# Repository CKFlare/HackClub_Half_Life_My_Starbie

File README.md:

# HackClub Half Life: My Starbie

This week I made the starter project, a starbie.

my Starbie is BMO from adventure time. during the second week I will create a housing for it that resembles him from the show. I chose BMO simply because he is cute and I thought it was a good fit as he is a robot.

My starbie is very simple, it is just the basic starbie but with a passive buzzer added so it can react with sounds. I simply use the passive buzzer which is in the Arduino Uno R3 super starter kit so that I could buy as little as possible. This entire project is very simple honestly, I didn't do anything special other than put things on the backside of the pcb which is not described in the week one tutorial, still very simple though. this means all it has is:

- a 128x64 pixel screen
- a motion sensor
- a tempurature and humdity sensor
- 2 push buttons

sorry for the horribly ugly schematic

*I own the passive buzzer and the DHT11 therefore they are not found in the bill of materials

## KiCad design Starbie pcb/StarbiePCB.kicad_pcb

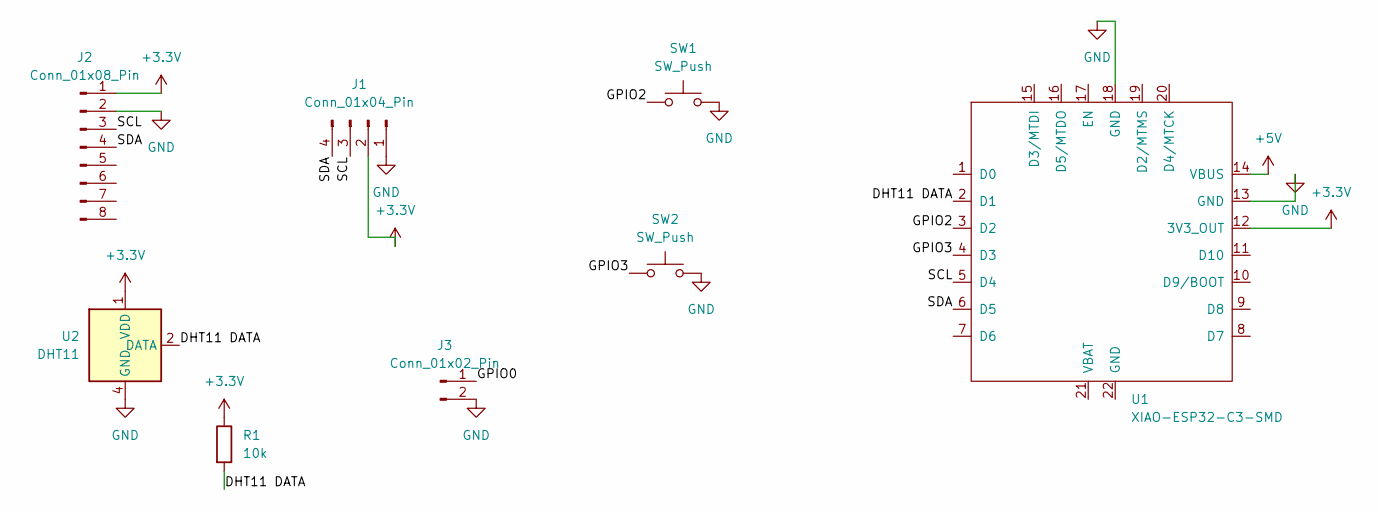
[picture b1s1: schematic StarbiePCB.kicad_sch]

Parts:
J1: Conn_01x04_Pin; Display_128x64_096_I2C
J2: Conn_01x08_Pin; PinHeader_1x08_P2.54mm_Vertical
J3: Conn_01x02_Pin; Buzzer_12x9.5RM7.6
R1: 10k; R_Axial_DIN0204_L3.6mm_D1.6mm_P7.62mm_Horizontal
SW1, SW2: SW_Push; SW_Cherry_MX_1.00u_PCB
U1: XIAO-ESP32-C3-SMD
U2: DHT11; Aosong_DHT11_5.5x12.0_P2.54mm

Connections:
+3.3V: J1.2, J2.1, R1.1, U1.12 (3V3_OUT), U2.1 (VDD)
+5V: U1.14 (VBUS)
/DHT11 DATA: R1.2, U1.2 (D1), U2.2 (DATA)
/GPIO0: J3.1, U1.1 (D0)
/GPIO2: SW1.1, U1.3 (D2)
/GPIO3: SW2.1, U1.4 (D3)
/SCL: J1.3, J2.3, U1.5 (D4)
/SDA: J1.4, J2.4, U1.6 (D5)
GND: J1.1, J2.2, J3.2, SW1.2, SW2.2, U1.13 (GND), U1.18 (GND), U2.4 (GND)

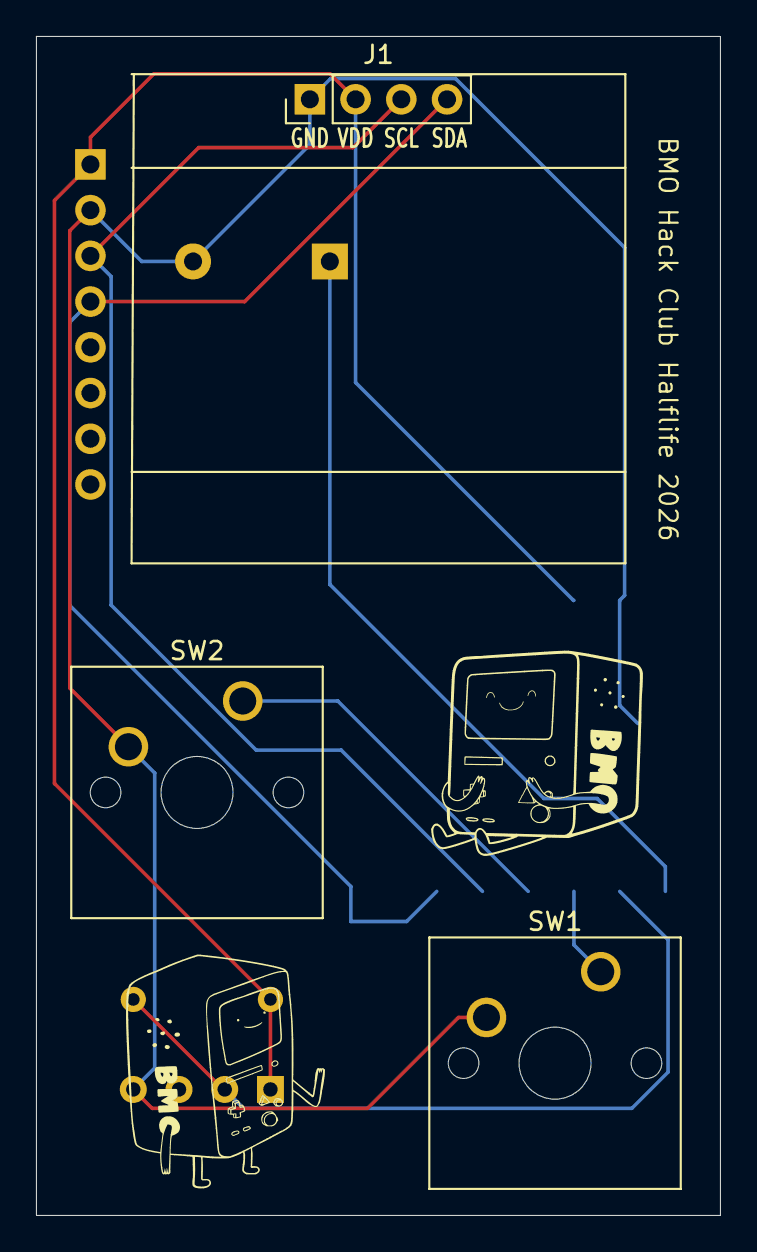
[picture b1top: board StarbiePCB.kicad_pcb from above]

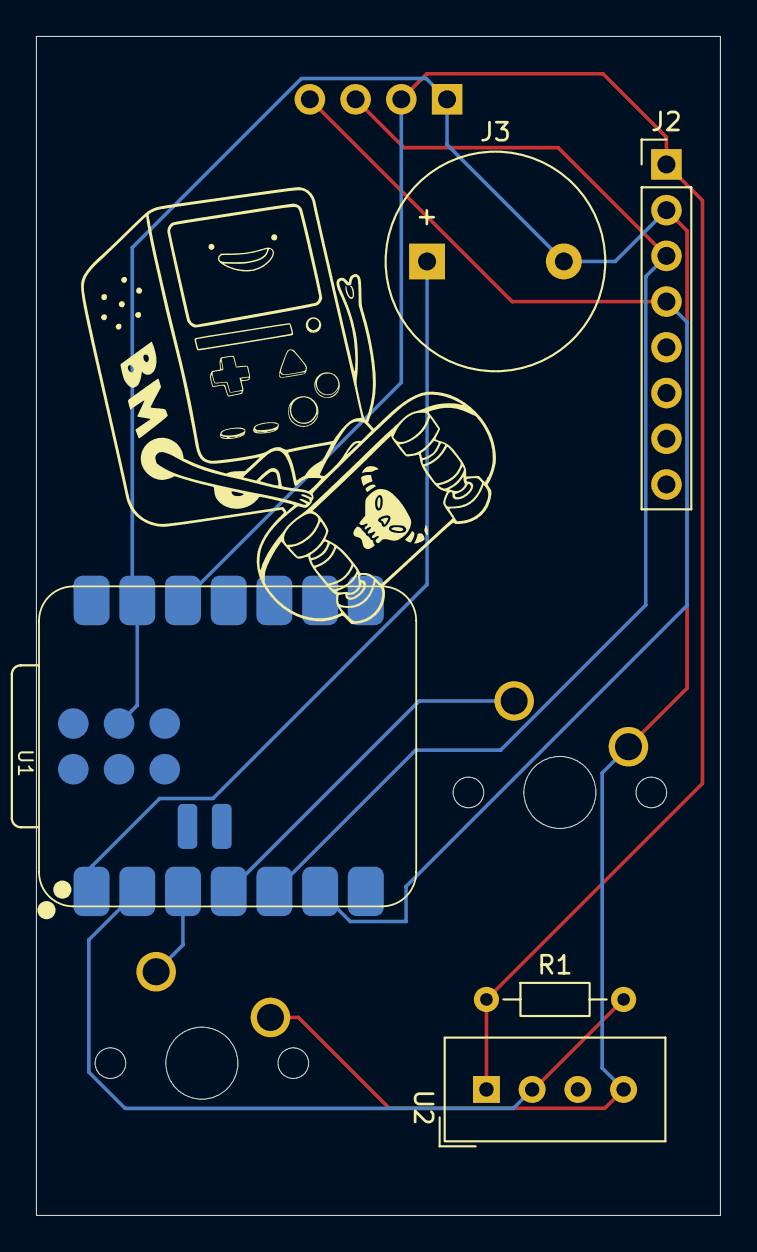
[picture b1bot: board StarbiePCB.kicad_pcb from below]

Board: 2 copper layers, 38.0 x 65.5 mm, 8 parts (5 on the bottom side), 8 nets.
